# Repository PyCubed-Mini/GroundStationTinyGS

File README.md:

# GroundStationTinyGS

Hardware wiki: https://github.com/PyCubed-Mini/NewDocumentation/wiki/Ground-Control-Hardware  
Software wiki: https://github.com/PyCubed-Mini/NewDocumentation/wiki/Ground-Control-Software

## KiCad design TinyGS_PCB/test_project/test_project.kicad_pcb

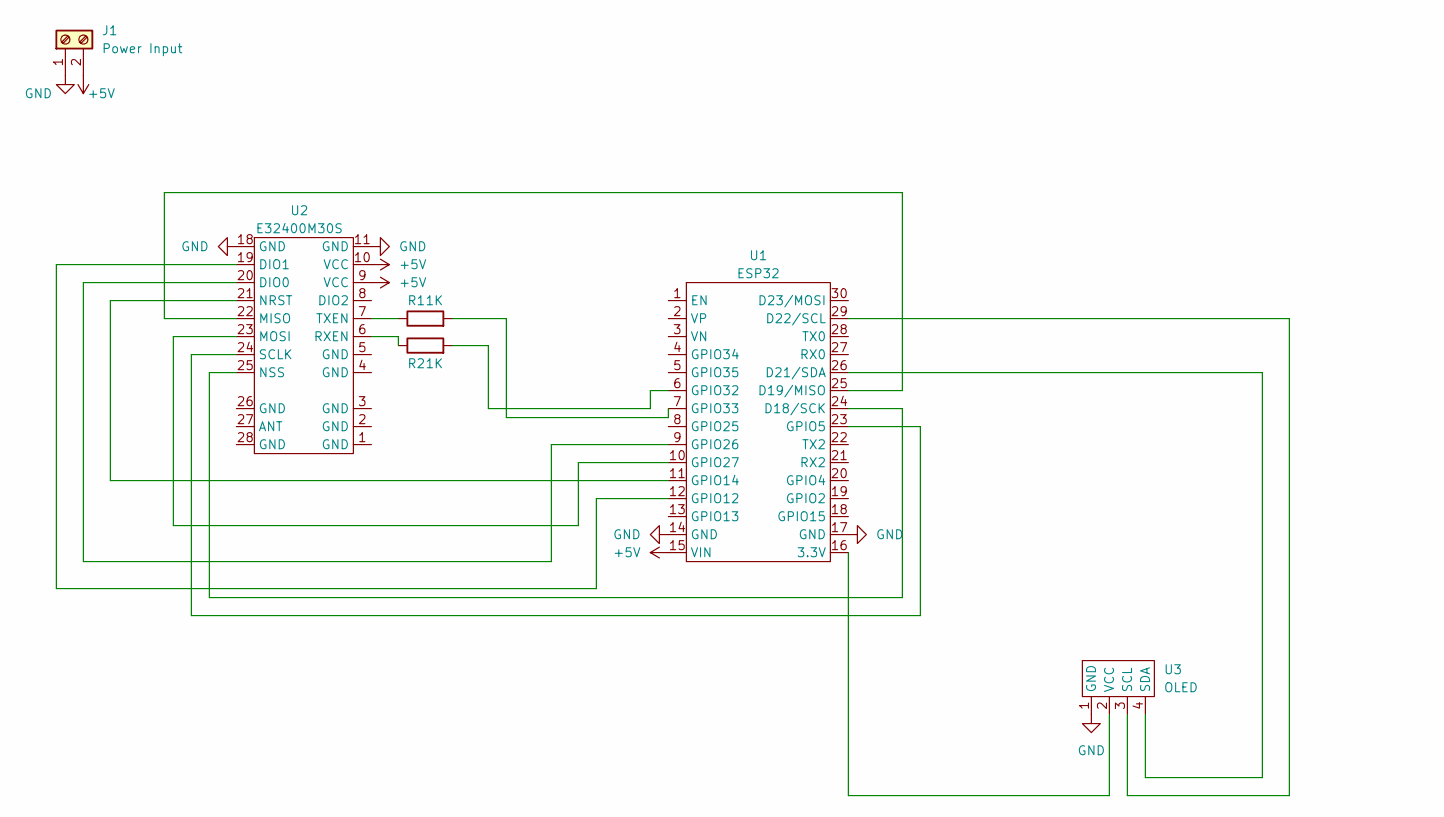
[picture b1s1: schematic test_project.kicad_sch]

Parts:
J1: Power Input; TerminalBlock_4Ucon_1x02_P3.50mm_Horizontal
R1, R2: 1K; R_Axial_DIN0207_L6.3mm_D2.5mm_P10.16mm_Horizontal
U1: ESP32
U2: E32400M30S; E32400M
U3: OLED

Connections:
+5V: J1.2, U1.15 (VIN), U2.9 (VCC), U2.10 (VCC)
GND: J1.1, U1.14 (GND), U1.17 (GND), U2.11 (GND), U2.18 (GND), U3.1 (GND)
unnamed: R1.1, U2.7 (TXEN)
unnamed: R1.2, U1.7 (GPIO33)
unnamed: R2.1, U2.6 (RXEN)
unnamed: R2.2, U1.6 (GPIO32)
unnamed: U1.9 (GPIO26), U2.20 (DIO0)
unnamed: U1.10 (GPIO27), U2.23 (MOSI)
unnamed: U1.11 (GPIO14), U2.21 (NRST)
unnamed: U1.12 (GPIO12), U2.19 (DIO1)
unnamed: U1.16 (3.3V), U3.2 (VCC)
unnamed: U1.23 (GPIO5), U2.24 (SCLK)
unnamed: U1.24 (D18/SCK), U2.25 (NSS)
unnamed: U1.25 (D19/MISO), U2.22 (MISO)
unnamed: U1.26 (D21/SDA), U3.4 (SDA)
unnamed: U1.29 (D22/SCL), U3.3 (SCL)

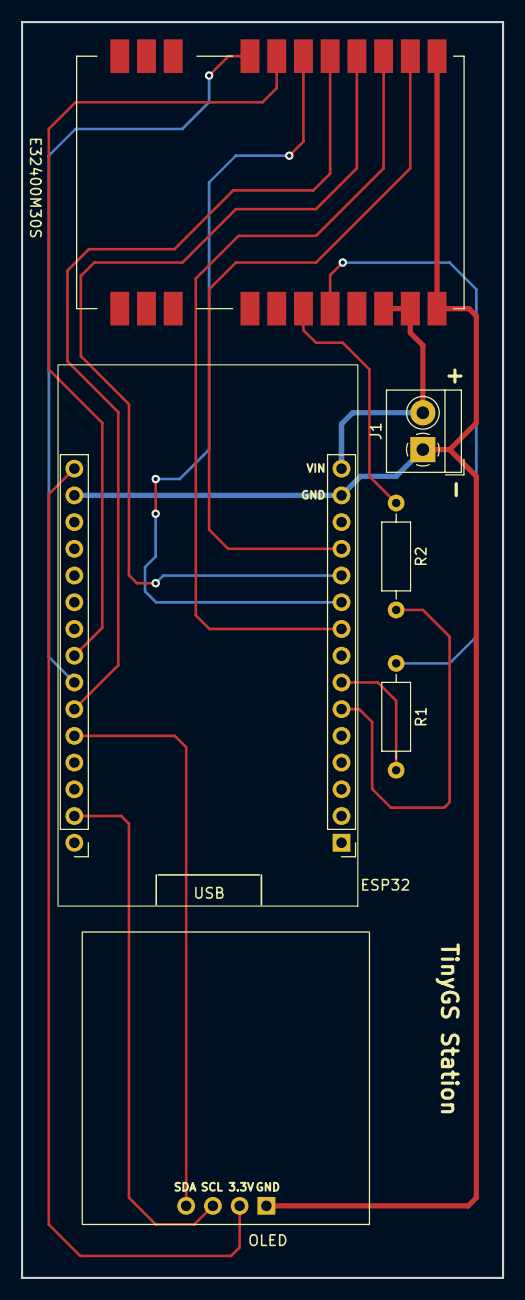
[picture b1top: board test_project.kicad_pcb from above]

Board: 2 copper layers, 45.7 x 119.4 mm, 6 parts (0 on the bottom side), 16 nets.

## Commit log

2022-05-16 Finished schematic and PCB for the TinyGS Station
2022-05-26 Added the software change needed for the SX1278 chip to get work with tinygs
2022-05-26 edits
2022-06-04 fixed mistakes on pcb and software
